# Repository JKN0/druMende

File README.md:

# druMende

Drumende is an analog drum machine in 70's style. All circuitry is designed so that it could have been built in the late 70's/early 80's.
All sound generators are analog, using transistors and op amps. Sequencer is without microcontroller, only 7400/4000-series discrete logic.

Soundgenerators are modeled according to classic drum machines and also newer designs:
- Boss DR-55: bass drum, snare drum, hi-hat, accent-circuit
- Korg KR-55: bass drum, snare drum, rimshot, claves, noise generator
- Andromeda Space Rockers by Eric Archer: hi-hat, tom hi, tom lo
- 7400 contest entry by Matt Sarnoff: sequencer

The goal has not been to duplicate the original circuits as close as possible. There are several modifications to original circuits.
Also sequencer has experienced serious modifications.

There are 10 sound generators. Because sequencer has only 6 voice channels + accent channel, sound for four channels is selectable.
Each channel level can be controlled with level control knobs. Also each channel has one controllable parameter, tuning or decay time.

Sequencer is 7 channel, 16 steps. Two 7 x 16 step patterns can be stored.

Demonstration video: https://youtu.be/f7uYuddqCkw

A more detailed build log is here: https://retroandreverse.blogspot.com/2020/12/analog-drums-beginnings-drumshave.html

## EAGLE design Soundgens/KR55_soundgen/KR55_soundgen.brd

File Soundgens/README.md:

# Sound generators

Sound generators are divided in four circuit boards:

- DR-55 soundgen
-- 3 generators: DR-55 BD, SD, HH
- KR-55 soundgen
-- 3 generators: KR-55 BD, SD; ASR MK2 HH
- Perc soundgen
-- 4 generators: KR-55 rimshot, claves; ASR MK1 hi-tom, lo-tom
- Main mixer
-- main mixer, accent submixer, accent circuit, noise generator

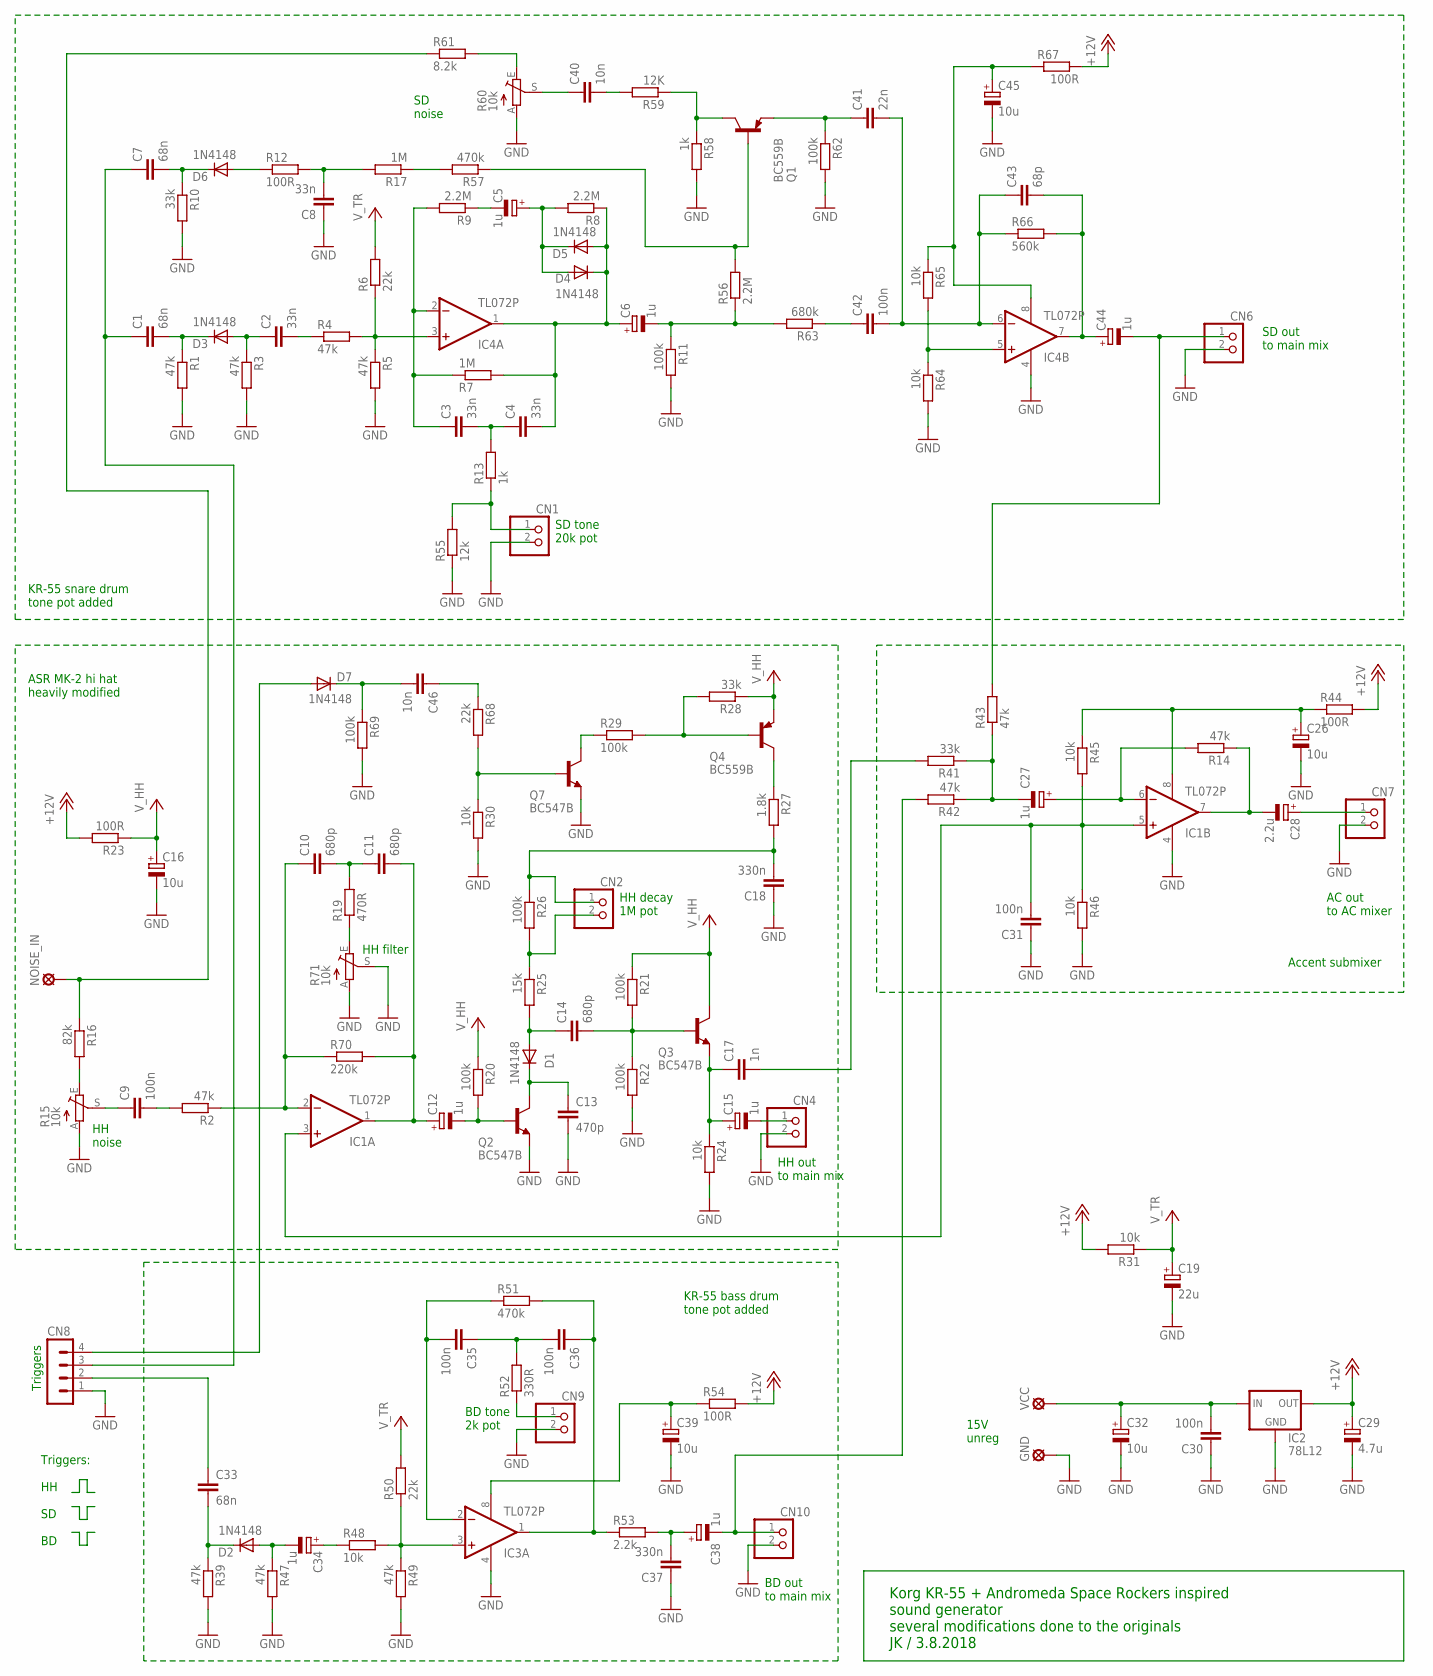
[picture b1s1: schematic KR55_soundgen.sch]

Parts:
C1, C7, C33: 68n; C0805
C2, C3, C4, C8: 33n; C0805
C5, C6, C12, C15, C27, C34, C38, C44: 1u; SMC_A
C9, C30, C31, C35, C36: 100n; C0805
C10, C11, C14: 680p; C0805
C13: 470p; C0805
C16, C32, C39, C45: 10u; E2,5-5
C17: 1n; C0805
C18, C37: 330n; C0805
C19: 22u; E2,5-5
C26: 10u; E5-5
C28: 2.2u; SMC_A
C29: 4.7u; SMC_A
C40: 10n; C1206
C41: 22n; C0805
C42: 100n; C050-024X044
C43: 68p; C0805
C46: 10n; C0805
CN1, CN2, CN4, CN6, CN7, CN9, CN10: PINHD-1X2; 1X02
CN8: MA04-1
D1, D2, D3, D4, D5, D6: 1N4148; SOD80C
D7: 1N4148; DO35-10
GND: LSP10
IC1, IC3, IC4: TL072P; DIL08
IC2: 78L12; 78LXX
NOISE_IN: LSP10
Q1, Q4: BC559B; TO92-EBC
Q2, Q3, Q7: BC547B; TO92
R1, R2, R3, R4, R5, R14, R39, R42, R43, R47, R49: 47k; R0805
R6, R50, R68: 22k; R0805
R7, R17: 1M; R0805
R8, R9, R56: 2.2M; R0805
R10, R28, R41: 33k; R0805
R11, R21, R22, R26, R29, R62, R69: 100k; R0805
R12, R23, R67: 100R; R0805
R13, R58: 1k; R0805
R15, R60, R71: 10k; S63X
R16: 82k; R0805
R19: 470R; 0207/10
R20: 100k; 0207/10
R24, R30, R31, R45, R46, R48, R64, R65: 10k; R0805
R25: 15k; 0207/10
R27: 1.8k; 0207/10
R44, R54: 100R; 0207/10
R51, R57: 470k; R0805
R52: 330R; R0805
R53: 2.2k; 0207/10
R55: 12k; R0805
R59: 12K; R0805
R61: 8.2k; R0805
R63: 680k; R0805
R66: 560k; R0805
R70: 220k; R0805
VCC: LSP10

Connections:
+12V: C29.+, IC2.OUT, R23.2, R31.2, R44.2, R54.2, R67.2
+15V: C30.2, C32.+, IC2.IN, VCC.MP
GND: C8.1, C13.2, C16.-, C18.1, C19.-, C26.-, C29.-, C30.1, C31.1, C32.-, C37.1, C39.-, C45.-, CN1.2, CN4.2, CN6.2, CN7.2, CN8.1, CN9.2, CN10.2, GND.MP, IC1.4 (V-), IC2.GND, IC3.4 (V-), IC4.4 (V-), Q2.1 (E), Q7.1 (E), R1.2, R3.2, R5.2, R10.2, R11.2, R15.A, R22.2, R24.2, R30.2, R39.2, R46.2, R47.2, R49.2, R55.1, R58.2, R60.A, R62.2, R64.2, R69.2, R71.A, R71.S
unnamed: C3.1, IC4.2 (-IN), R7.1, R9.2
unnamed: C4.2, C6.+, D4.C, D5.A, IC4.1 (OUT), R7.2, R8.1
unnamed: IC4.3 (+IN), R4.2, R5.1, R6.1
unnamed: C2.2, R4.1
unnamed: C2.1, D3.A, R3.1
unnamed: C1.2, D3.C, R1.1
unnamed: R15.E, R16.2
unnamed: CN1.1, R13.1, R55.2
unnamed: C9.1, R15.S
unnamed: C5.-, R9.1
unnamed: C5.+, D4.A, D5.C, R8.2
unnamed: R60.E, R61.2
unnamed: C9.2, R2.2
unnamed: R19.1, R71.E
unnamed: C12.-, Q2.2 (B), R20.2
unnamed: C11.2, C12.+, IC1.1 (OUT), R70.2
unnamed: C13.1, D1.C, Q2.3 (C)
unnamed: C10.1, IC1.2 (-IN), R2.1, R70.1
unnamed: C10.2, C11.1, R19.2
unnamed: C14.1, D1.A, R25.2
unnamed: C14.2, Q3.2 (B), R21.2, R22.1
unnamed: C41.2, C42.2, C43.1, IC4.6 (-IN), R66.1
unnamed: C35.2, IC3.2 (-IN), R51.1
unnamed: C15.+, C17.1, Q3.1 (E), R24.1
unnamed: CN2.2, R25.1, R26.2
unnamed: C18.2, CN2.1, R26.1, R27.2
unnamed: C8.2, R12.2, R17.2
unnamed: Q4.C, R27.1
unnamed: R17.1, R57.2
unnamed: C27.-, R41.1, R42.1, R43.1
unnamed: C28.-, IC1.7 (OUT), R14.1
unnamed: C27.+, IC1.6 (-IN), R14.2
unnamed: C36.1, IC3.1 (OUT), R51.2, R53.1
unnamed: C35.1, C36.2, R52.2
unnamed: CN9.1, R52.1
unnamed: IC3.3 (+IN), R48.2, R49.1, R50.1
unnamed: C34.+, R48.1
unnamed: C34.-, D2.A, R47.1
unnamed: C33.2, D2.C, R39.1
unnamed: C37.2, C38.+, R53.2
unnamed: C3.2, C4.1, R13.2
unnamed: C40.1, R60.S
unnamed: D6.A, R12.1
unnamed: C7.2, D6.C, R10.1
unnamed: C40.2, R59.2
unnamed: Q1.C, R58.1, R59.1
unnamed: Q1.B, R56.2, R57.1
unnamed: C6.-, R11.1, R56.1, R63.2
unnamed: C42.1, R63.1
unnamed: C41.1, Q1.E, R62.1
unnamed: IC4.5 (+IN), R64.1, R65.2
unnamed: C43.2, C44.+, IC4.7 (OUT), R66.2
unnamed: C45.+, IC4.8 (V+), R65.1, R67.1
unnamed: Q4.B, R28.2, R29.2
unnamed: Q7.3 (C), R29.1
unnamed: Q7.2 (B), R30.1, R68.2
unnamed: C46.1, R68.1
unnamed: C46.2, D7.C, R69.1
NOISE_IN: NOISE_IN.MP, R16.1, R61.1
OUT_AC: C28.+, CN7.1
OUT_BD: C38.-, CN10.1, R42.2
OUT_HH: C15.-, CN4.1
OUT_HH_AC: C17.2, R41.2
OUT_SD: C44.-, CN6.1, R43.2
TRIG_BD: C33.1, CN8.2
TRIG_HH: CN8.4, D7.A
TRIG_SD: C1.1, C7.1, CN8.3
V_BD: C39.+, IC3.8 (V+), R54.1
V_HH: C16.+, Q3.3 (C), Q4.E, R20.1, R21.1, R23.1, R28.1
V_MX: C26.+, IC1.8 (V+), R44.1, R45.1
V_MX/2: C31.2, IC1.3 (+IN), IC1.5 (+IN), R45.2, R46.1
V_TR: C19.+, R6.2, R31.1, R50.2

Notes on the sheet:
Triggers
SD tone 20k pot
HH decay 1M pot
HH out to main mix
AC out to AC mixer
15V unreg
KR-55 bass drum tone pot added
KR-55 snare drum tone pot added
ASR MK-2 hi hat heavily modified
Accent submixer
Korg KR-55 + Andromeda Space Rockers inspired sound generator several modifications done to the originals JK / 3.8.2018
SD noise
BD out to main mix
BD tone 2k pot
SD out to main mix
HH noise
HH filter
Triggers: HH SD BD

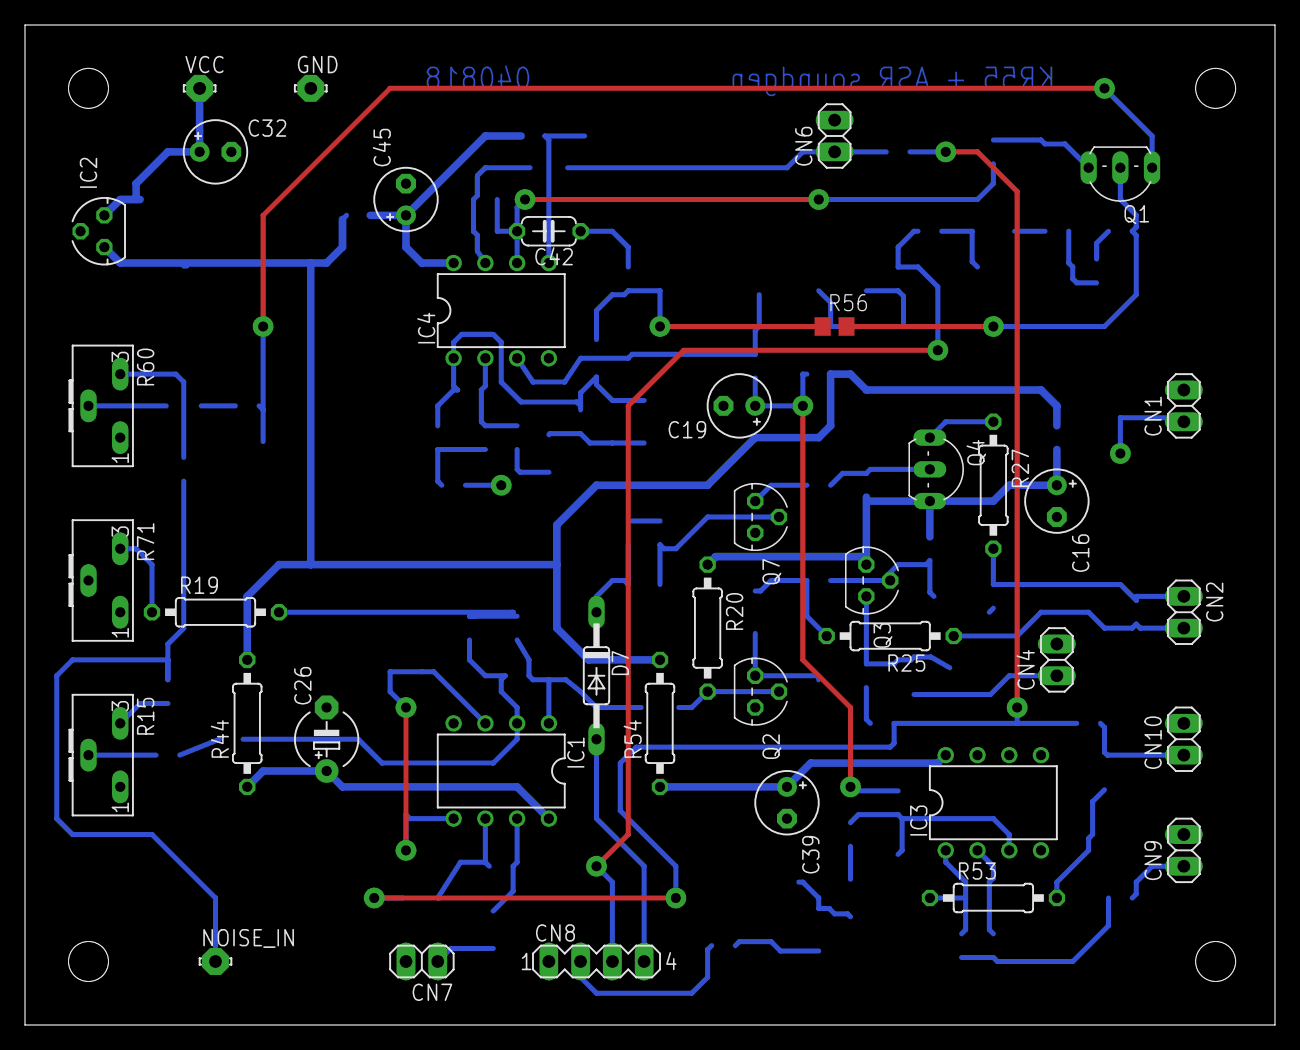
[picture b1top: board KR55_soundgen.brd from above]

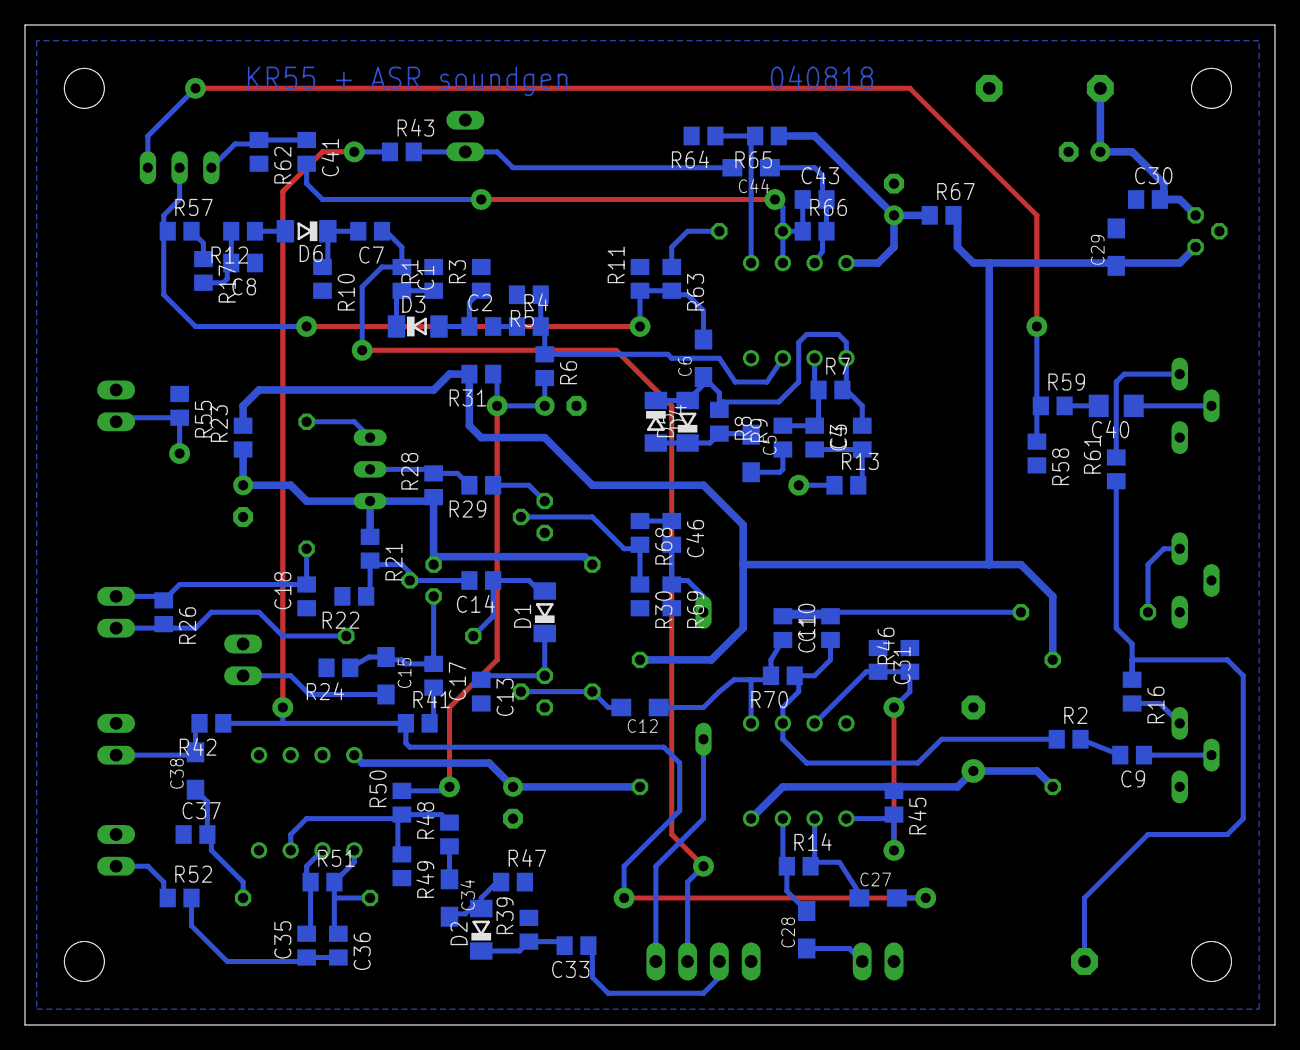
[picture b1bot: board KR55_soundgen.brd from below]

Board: 2 copper layers, 100.0 x 80.0 mm, 129 parts (90 on the bottom side), 75 nets.

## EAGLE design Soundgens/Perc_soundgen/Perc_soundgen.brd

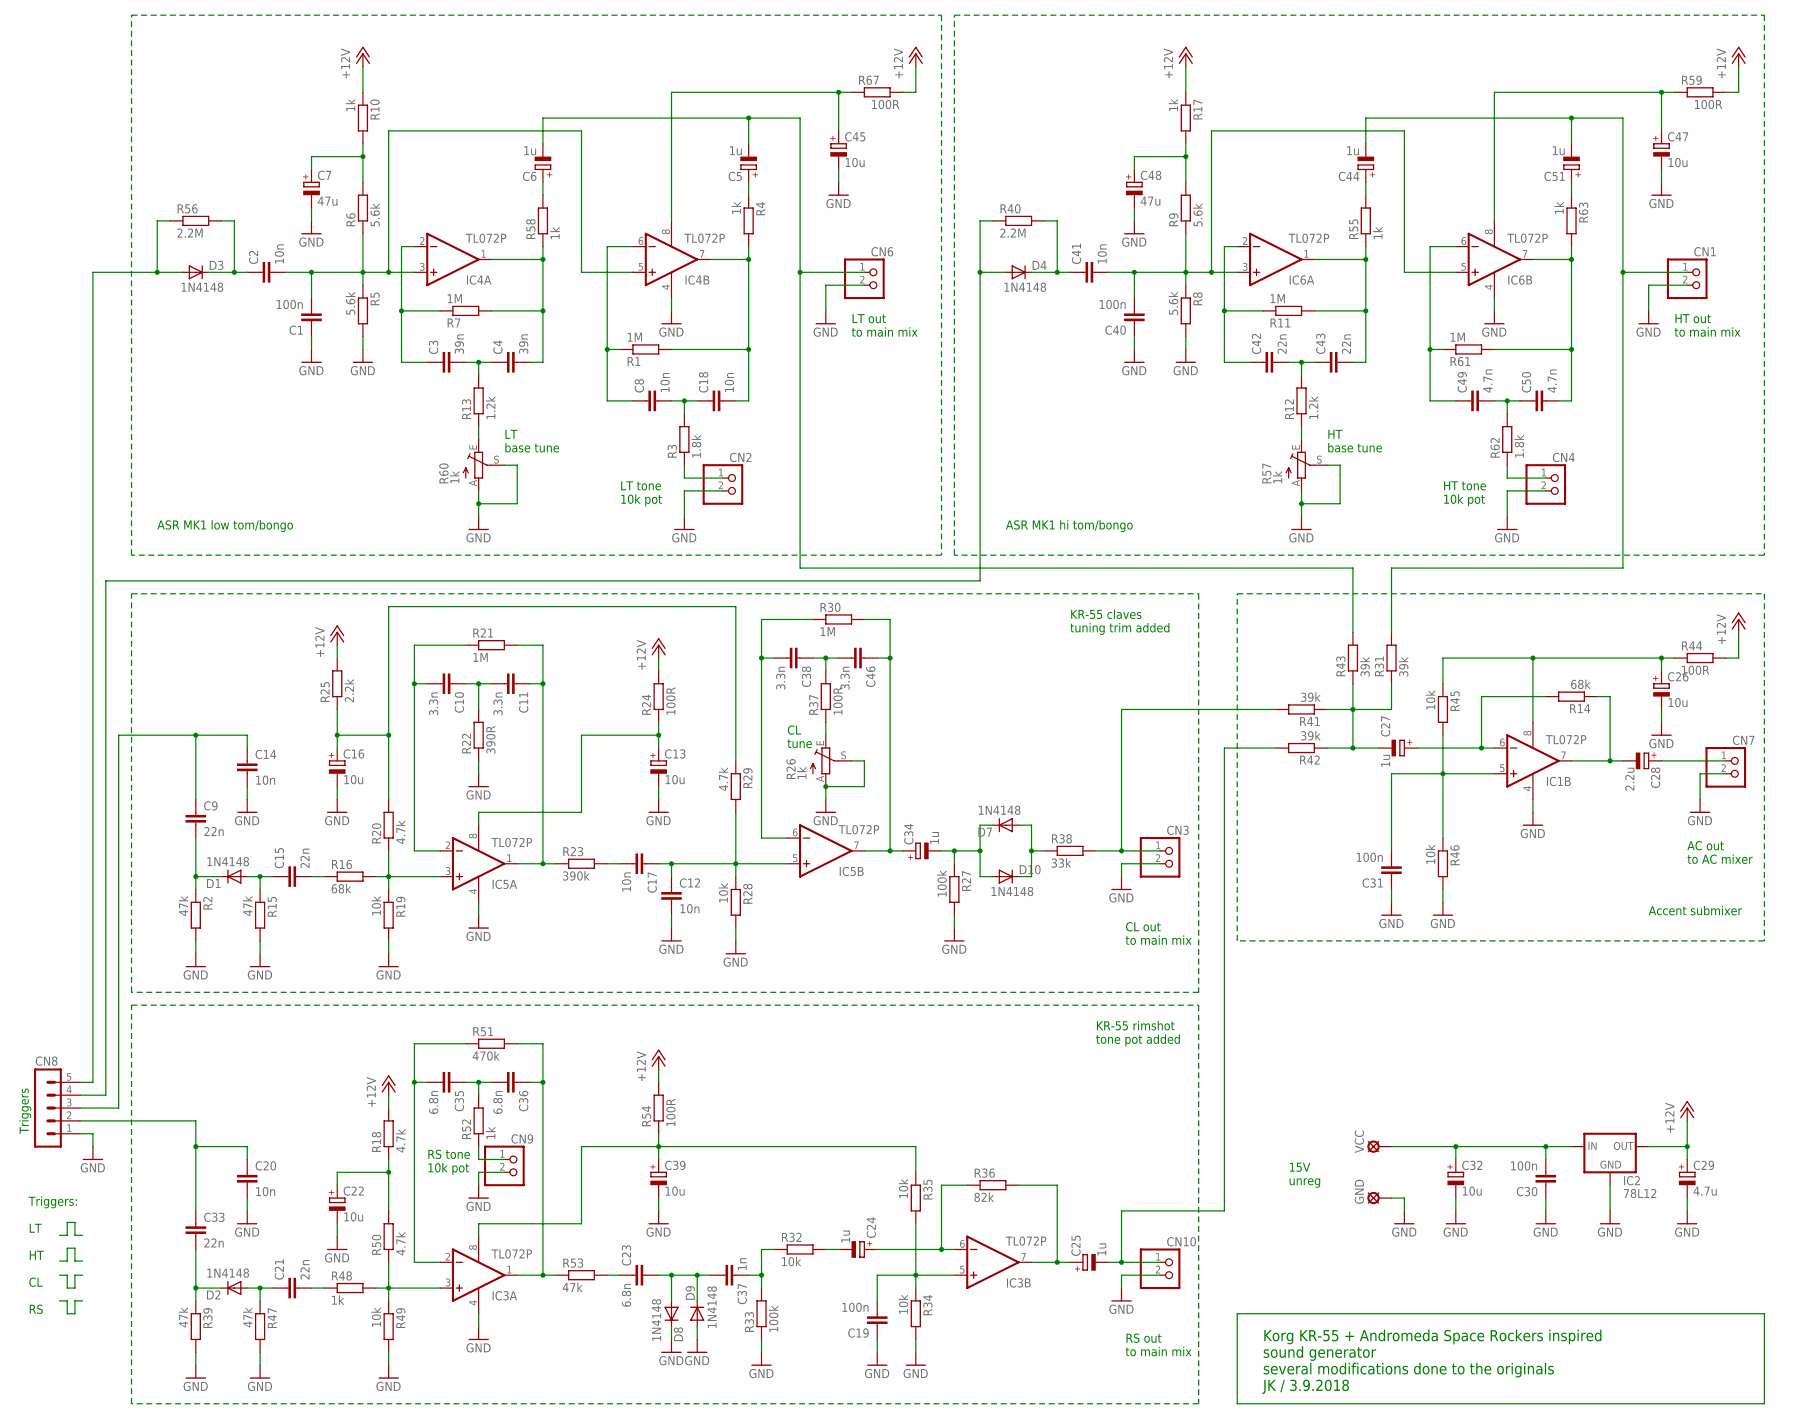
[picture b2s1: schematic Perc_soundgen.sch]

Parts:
C1, C19, C30, C31, C40: 100n; C0805
C2, C8, C12, C14, C17, C18, C20, C41: 10n; C0603
C3, C4: 39n; C0805
C5, C6, C24, C25, C27, C34, C44, C51: 1u; SMC_A
C7, C48: 47u; E2,5-5
C9, C15, C21, C42, C43: 22n; C0805
C10, C11, C38, C46: 3.3n; C0805
C13, C16, C22, C26, C32, C39, C45, C47: 10u; E2,5-5
C23, C35, C36: 6.8n; C0805
C28: 2.2u; SMC_A
C29: 4.7u; SMC_A
C33: 22n; C075-032X103
C37: 1n; C0805
C49, C50: 4.7n; C0805
CN1, CN2, CN3, CN4, CN6, CN7, CN9, CN10: PINHD-1X2; 1X02
CN8: MA05-1
D1, D2, D3, D4, D7, D8, D9, D10: 1N4148; SOD80C
GND: LSP10
IC1, IC3, IC4, IC5, IC6: TL072P; DIL08
IC2: 78L12; 78LXX
R1, R7, R11, R21, R30, R61: 1M; R0805
R2, R15, R39, R47: 47k; R0805
R3, R62: 1.8k; R0805
R4, R55, R58, R63: 1k; 0207/10
R5, R6, R8, R9: 5.6k; R0805
R10, R17, R48, R52: 1k; R0805
R12: 1.2k; R0805
R13: 1.2k; 0207/12
R14, R16: 68k; R0805
R18, R29: 4.7k; 0207/10
R19, R28, R32, R34, R35, R45, R46, R49: 10k; R0805
R20, R50: 4.7k; R0805
R22: 390R; R1206
R23: 390k; 0207/10
R24, R37, R44, R54, R59, R67: 100R; R0805
R25: 2.2k; R0805
R26, R57, R60: 1k; S63X
R27, R33: 100k; R0805
R31, R41, R42, R43: 39k; R0805
R36: 82k; R0805
R38: 33k; R0805
R40, R56: 2.2M; R0805
R51: 470k; R0805
R53: 47k; 0207/10
VCC: LSP10

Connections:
+12V: C29.+, IC2.OUT, R10.1, R17.1, R18.2, R24.2, R25.2, R44.2, R54.2, R59.2, R67.2
+15V: C30.2, C32.+, IC2.IN, VCC.MP
GND: C1.1, C7.-, C12.2, C13.-, C14.2, C16.-, C19.1, C20.2, C22.-, C26.-, C29.-, C30.1, C31.1, C32.-, C39.-, C40.1, C45.-, C47.-, C48.-, CN1.2, CN2.2, CN3.2, CN4.2, CN6.2, CN7.2, CN8.1, CN9.2, CN10.2, D8.C, D9.A, GND.MP, IC1.4 (V-), IC2.GND, IC3.4 (V-), IC4.4 (V-), IC5.4 (V-), IC6.4 (V-), R2.2, R5.2, R8.2, R15.2, R19.2, R22.1, R26.A, R26.S, R27.2, R28.2, R33.1, R34.2, R39.2, R46.2, R47.2, R49.2, R57.A, R57.S, R60.A, R60.S
unnamed: C3.1, IC4.2 (-IN), R7.1
unnamed: C4.2, IC4.1 (OUT), R7.2, R58.1
unnamed: C1.2, C2.2, IC4.3 (+IN), IC4.5 (+IN), R5.1, R6.1
unnamed: C6.+, R58.2
unnamed: C7.+, R6.2, R10.2
unnamed: C18.2, IC4.7 (OUT), R1.2, R4.2
unnamed: R13.1, R60.E
unnamed: C10.2, IC5.2 (-IN), R21.1
unnamed: C2.1, D3.C, R56.2
unnamed: C23.2, R53.2
unnamed: CN2.1, R3.1
unnamed: C11.1, IC5.1 (OUT), R21.2, R23.1
unnamed: C10.1, C11.2, R22.2
unnamed: R26.E, R37.1
unnamed: IC5.3 (+IN), R16.2, R19.1, R20.1
unnamed: C15.2, R16.1
unnamed: C15.1, D1.A, R15.1
unnamed: C9.2, D1.C, R2.1
unnamed: C16.+, R20.2, R25.1, R29.1
unnamed: C38.2, IC5.6 (-IN), R30.1
unnamed: C8.1, IC4.6 (-IN), R1.1
unnamed: C35.2, IC3.2 (-IN), R51.1
unnamed: C12.1, C17.1, IC5.5 (+IN), R28.1, R29.2
unnamed: C34.-, D7.C, D10.A, R27.1
unnamed: C34.+, C46.1, IC5.7 (OUT), R30.2
unnamed: C8.2, C18.1, R3.2
unnamed: C17.2, R23.2
unnamed: C24.+, IC3.6 (-IN), R36.1
unnamed: C22.+, R18.1, R50.2
unnamed: C24.-, R32.2
unnamed: C19.2, IC3.5 (+IN), R34.1, R35.2
unnamed: D7.A, D10.C, R38.1
unnamed: C37.1, R32.1, R33.2
unnamed: C27.-, R31.1, R41.1, R42.1, R43.1
unnamed: C28.-, IC1.7 (OUT), R14.1
unnamed: C27.+, IC1.6 (-IN), R14.2
unnamed: C23.1, C37.2, D8.A, D9.C
unnamed: C36.1, IC3.1 (OUT), R51.2, R53.1
unnamed: C35.1, C36.2, R52.2
unnamed: CN9.1, R52.1
unnamed: IC3.3 (+IN), R48.2, R49.1, R50.1
unnamed: C21.2, R48.1
unnamed: C21.1, D2.A, R47.1
unnamed: C33.2, D2.C, R39.1
unnamed: C38.1, C46.2, R37.2
unnamed: C25.+, IC3.7 (OUT), R36.2
unnamed: C3.2, C4.1, R13.2
unnamed: C5.+, R4.1
unnamed: C43.2, IC6.1 (OUT), R11.2, R55.1
unnamed: C40.2, C41.2, IC6.3 (+IN), IC6.5 (+IN), R8.1, R9.1
unnamed: C42.1, IC6.2 (-IN), R11.1
unnamed: C42.2, C43.1, R12.2
unnamed: C47.+, IC6.8 (V+), R59.1
unnamed: C48.+, R9.2, R17.2
unnamed: C41.1, D4.C, R40.2
unnamed: C50.2, IC6.7 (OUT), R61.2, R63.2
unnamed: CN4.1, R62.1
unnamed: C49.1, IC6.6 (-IN), R61.1
unnamed: C49.2, C50.1, R62.2
unnamed: R12.1, R57.E
unnamed: C45.+, IC4.8 (V+), R67.1
unnamed: C44.+, R55.2
unnamed: C51.+, R63.1
OUT_AC: C28.+, CN7.1
OUT_CL: CN3.1, R38.2, R41.2
OUT_HT: C44.-, C51.-, CN1.1, R31.2
OUT_LT: C5.-, C6.-, CN6.1, R43.2
OUT_RS: C25.-, CN10.1, R42.2
TRIG_CL: C9.1, C14.1, CN8.3
TRIG_HT: CN8.4, D4.A, R40.1
TRIG_LT: CN8.5, D3.A, R56.1
TRIG_RS: C20.1, C33.1, CN8.2
V_BD: C39.+, IC3.8 (V+), R35.1, R54.1
V_BD1: C13.+, IC5.8 (V+), R24.1
V_MX: C26.+, IC1.8 (V+), R44.1, R45.1
V_MX/2: C31.2, IC1.5 (+IN), R45.2, R46.1

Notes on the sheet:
Triggers
AC out to AC mixer
15V unreg
KR-55 rimshot tone pot added
ASR MK1 low tom/bongo
Accent submixer
Korg KR-55 + Andromeda Space Rockers inspired sound generator several modifications done to the originals JK / 3.9.2018
LT base tune
RS out to main mix
RS tone 10k pot
LT out to main mix
Triggers: LT HT CL RS
KR-55 claves tuning trim added
CL out to main mix
CL tune
LT tone 10k pot
ASR MK1 hi tom/bongo
HT base tune
HT out to main mix
HT tone 10k pot

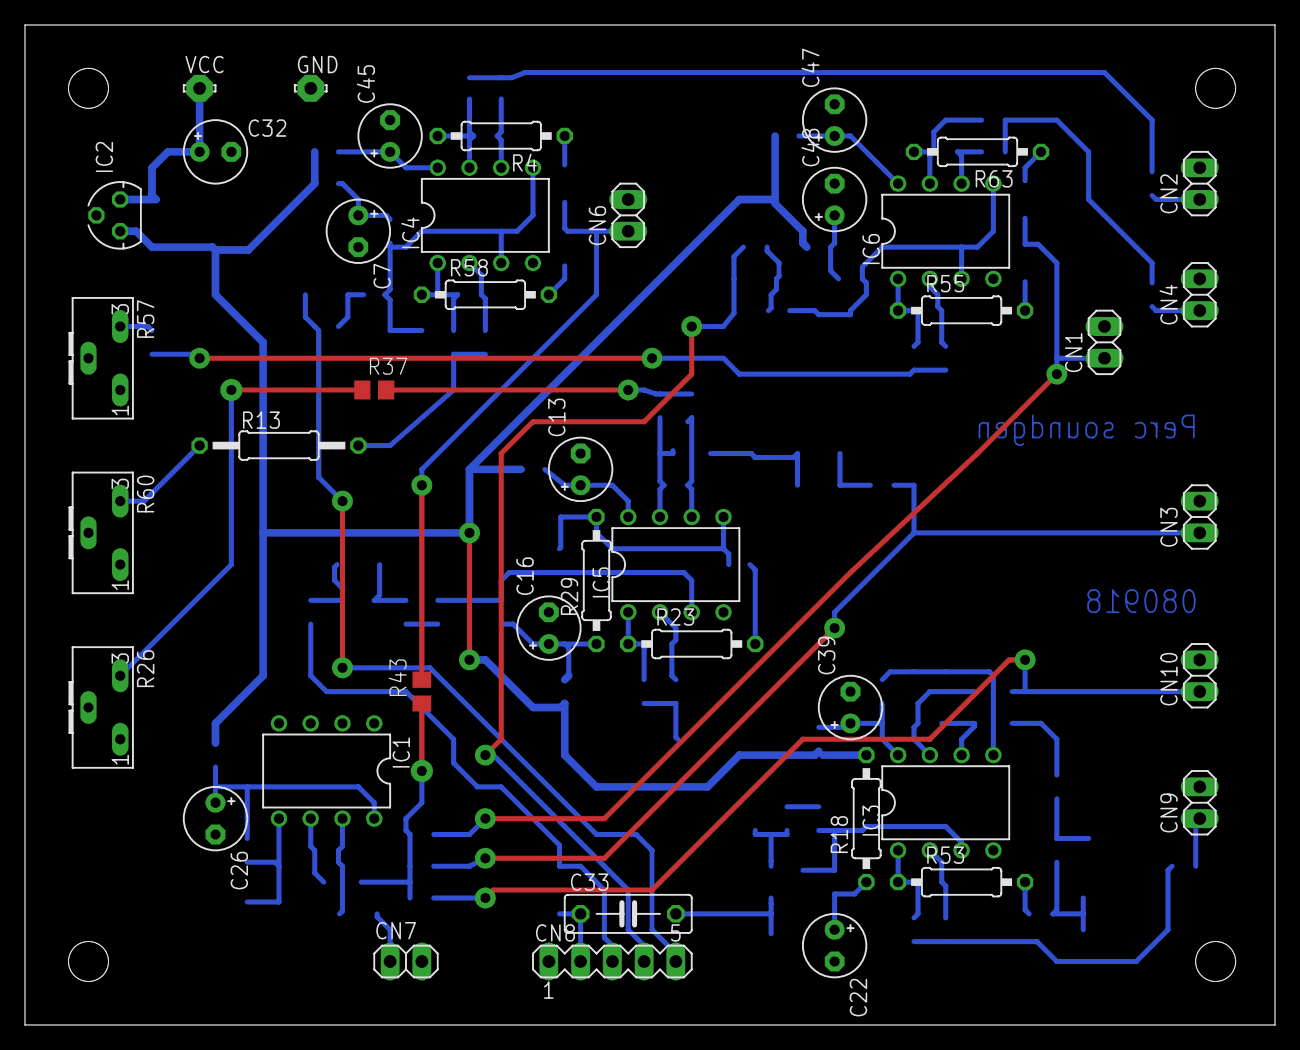
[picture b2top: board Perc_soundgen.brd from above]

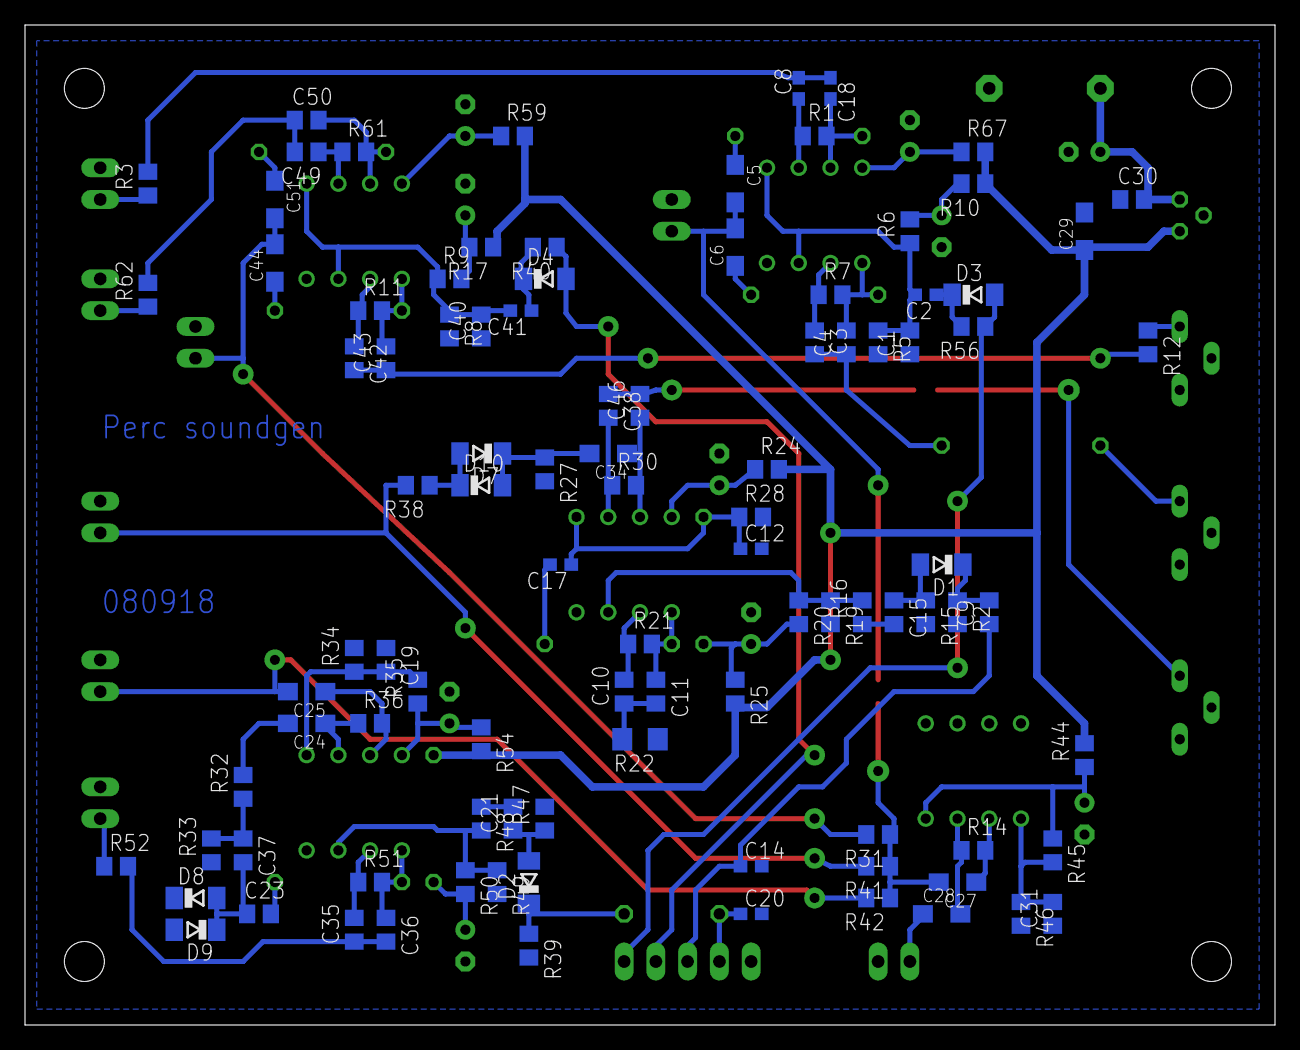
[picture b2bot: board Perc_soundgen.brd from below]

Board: 2 copper layers, 100.0 x 80.0 mm, 140 parts (98 on the bottom side), 79 nets.

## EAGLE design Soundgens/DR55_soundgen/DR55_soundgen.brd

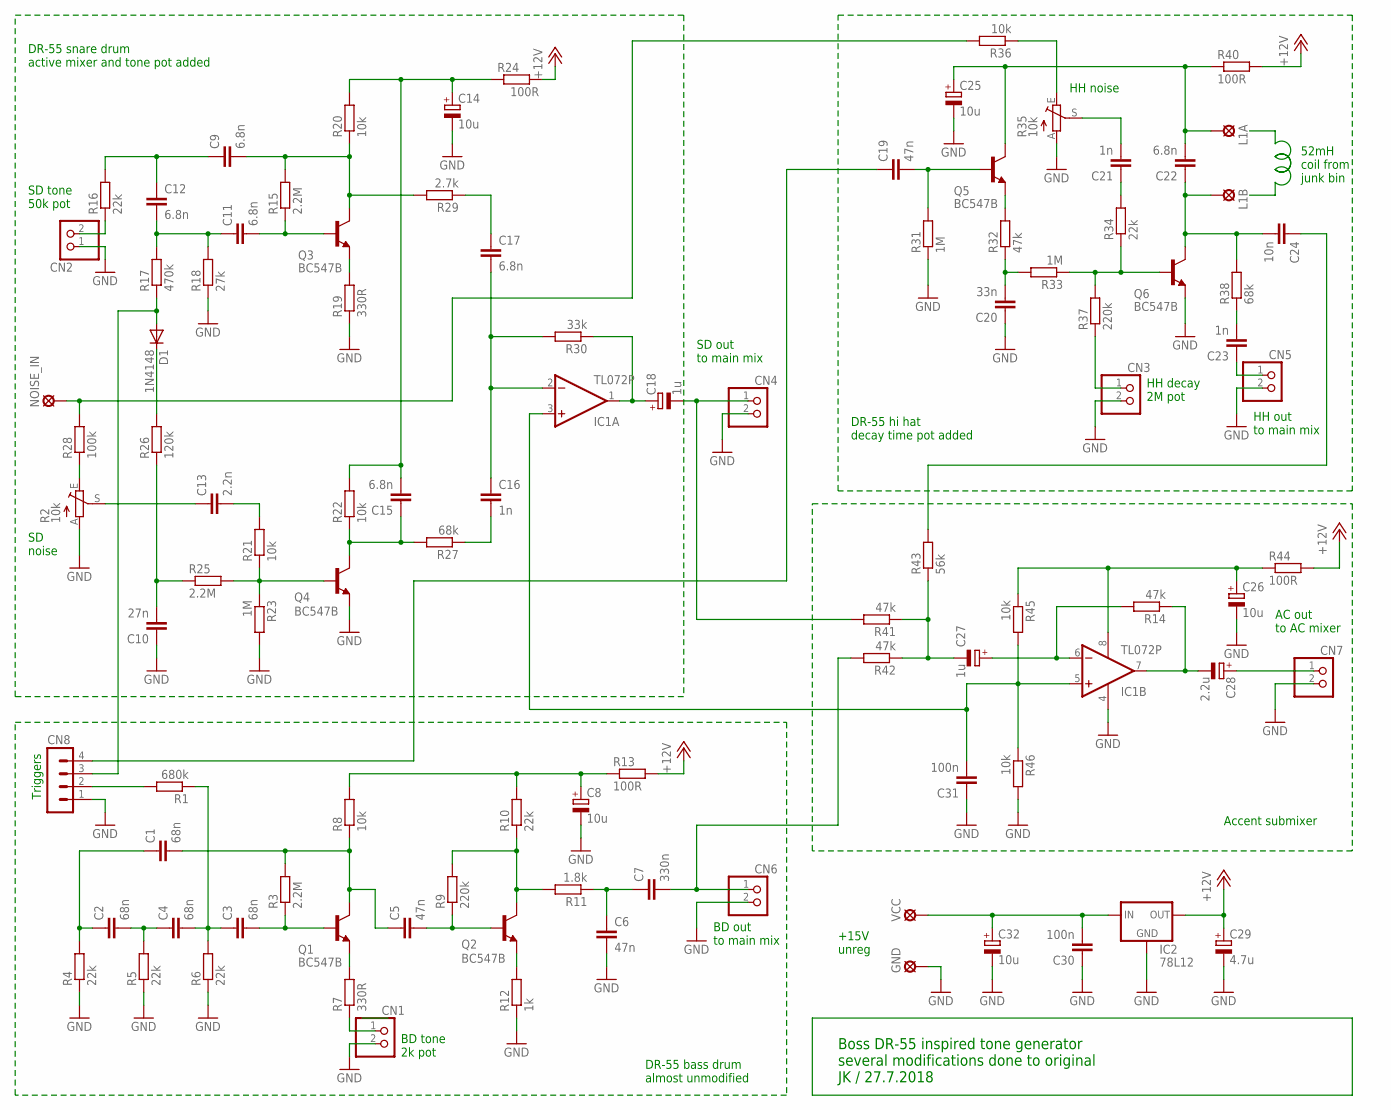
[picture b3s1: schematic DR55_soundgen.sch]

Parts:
C1, C2, C3, C4: 68n; C0805
C5, C6, C19: 47n; C0805
C7: 330n; C0805
C8, C14, C25, C26, C32: 10u; E5-5
C9, C11, C12, C17, C22: 6.8n; C0805
C10: 27n; C0805
C13: 2.2n; C0805
C15: 6.8n; C025-024X044
C16, C21, C23: 1n; C0805
C18, C27: 1u; SMC_A
C20: 33n; C0805
C24: 10n; C0805
C28: 2.2u; E5-5
C29: 4.7u; SMC_A
C30, C31: 100n; C0805
CN1, CN2, CN3, CN4, CN5, CN6, CN7: PINHD-1X2; 1X02
CN8: MA04-1
D1: 1N4148; SOD80C
GND: LSP10
IC1: TL072P; DIL08
IC2: 78L12; 78LXX
L1A, L1B: MCS10B
NOISE_IN: LSP10
Q1, Q2, Q3, Q4, Q5, Q6: BC547B; TO92
R1: 680k; R0805
R2, R35: 10k; S63X
R3, R15, R25: 2.2M; R0805
R4, R5, R6, R10, R16, R34: 22k; R0805
R7, R19: 330R; R0805
R8, R20, R21, R22, R36, R45, R46: 10k; R0805
R9, R37: 220k; R0805
R11: 1.8k; R0805
R12: 1k; R0805
R13, R24, R40, R44: 100R; R0805
R14, R41, R42: 47k; R0805
R17: 470k; R0805
R18: 27k; R0805
R23, R31, R33: 1M; R0805
R26: 120k; R0805
R27, R38: 68k; R0805
R28: 100k; R0805
R29: 2.7k; R0805
R30: 33k; R0805
R32: 47k; 0207/10
R43: 56k; R0805
VCC: LSP10

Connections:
+12V: C29.+, IC2.OUT, R13.2, R24.2, R40.2, R44.2
+15V: C30.2, C32.+, IC2.IN, VCC.MP
GND: C6.2, C8.-, C10.1, C14.-, C20.1, C25.-, C26.-, C29.-, C30.1, C31.1, C32.-, CN1.2, CN2.1, CN3.2, CN4.2, CN5.2, CN6.2, CN7.2, CN8.1, GND.MP, IC1.4 (V-), IC2.GND, Q4.1 (E), Q6.1 (E), R2.A, R4.1, R5.1, R6.1, R12.1, R18.1, R19.1, R23.2, R31.1, R35.A, R46.2
unnamed: C1.1, C2.1, R4.2
unnamed: C2.2, C4.1, R5.2
unnamed: C3.1, C4.2, R1.1, R6.2
unnamed: C3.2, Q1.2 (B), R3.1
unnamed: Q1.1 (E), R7.2
unnamed: CN1.1, R7.1
unnamed: C1.2, C5.1, Q1.3 (C), R3.2, R8.1
unnamed: C9.1, C12.1, R16.2
unnamed: C5.2, Q2.2 (B), R9.1
unnamed: R2.E, R28.1
unnamed: Q2.3 (C), R9.2, R10.1, R11.2
unnamed: Q2.1 (E), R12.2
unnamed: C6.1, C7.1, R11.1
unnamed: C11.1, C12.2, R17.2, R18.2
unnamed: C11.2, Q3.2 (B), R15.1
unnamed: Q3.1 (E), R19.2
unnamed: CN2.2, R16.1
unnamed: C9.2, Q3.3 (C), R15.2, R20.1, R29.2
unnamed: D1.C, R26.2
unnamed: C15.1, Q4.3 (C), R22.1, R27.2
unnamed: C10.2, R25.1, R26.1
unnamed: Q4.2 (B), R21.1, R23.1, R25.2
unnamed: C13.2, R21.2
unnamed: C16.2, R27.1
unnamed: C19.2, Q5.2 (B), R31.2
unnamed: C13.1, R2.S
unnamed: C17.1, R29.1
unnamed: C16.1, C17.2, IC1.2 (-IN), R30.2
unnamed: Q5.1 (E), R32.2
unnamed: C18.+, IC1.1 (OUT), R30.1
unnamed: C20.2, R32.1, R33.2
unnamed: Q6.2 (B), R33.1, R34.1, R37.2
unnamed: CN3.1, R37.1
unnamed: C22.1, C24.2, L1B.MP, Q6.3 (C), R38.2
unnamed: C23.2, R38.1
unnamed: C21.1, R34.2
unnamed: C21.2, R35.S
unnamed: R35.E, R36.1
unnamed: C27.-, R41.1, R42.1, R43.1
unnamed: C28.-, IC1.7 (OUT), R14.1
unnamed: C27.+, IC1.6 (-IN), R14.2
NOISE_IN: NOISE_IN.MP, R28.2, R36.2
OUT_AC: C28.+, CN7.1
OUT_BD: C7.2, CN6.1, R42.2
OUT_HH: C23.1, CN5.1
OUT_HH_AC: C24.1, R43.2
OUT_SD: C18.-, CN4.1, R41.2
TRIG_BD: CN8.2, R1.2
TRIG_HH: C19.1, CN8.4
TRIG_SD: CN8.3, D1.A, R17.1
V_BD: C8.+, R8.2, R10.2, R13.1
V_HH: C22.2, C25.+, L1A.MP, Q5.3 (C), R40.1
V_MX: C26.+, IC1.8 (V+), R44.1, R45.1
V_MX/2: C31.2, IC1.3 (+IN), IC1.5 (+IN), R45.2, R46.1
V_SD: C14.+, C15.2, R20.2, R22.2, R24.1

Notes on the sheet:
52mH coil from junk bin
Triggers
BD tone 2k pot
SD tone 50k pot
HH decay 2M pot
HH out to main mix
AC out to AC mixer
BD out to main mix
SD out to main mix
+15V unreg
DR-55 bass drum almost unmodified
DR-55 snare drum active mixer and tone pot added
DR-55 hi hat decay time pot added
Accent submixer
Boss DR-55 inspired tone generator several modifications done to original JK / 27.7.2018
HH noise
SD noise

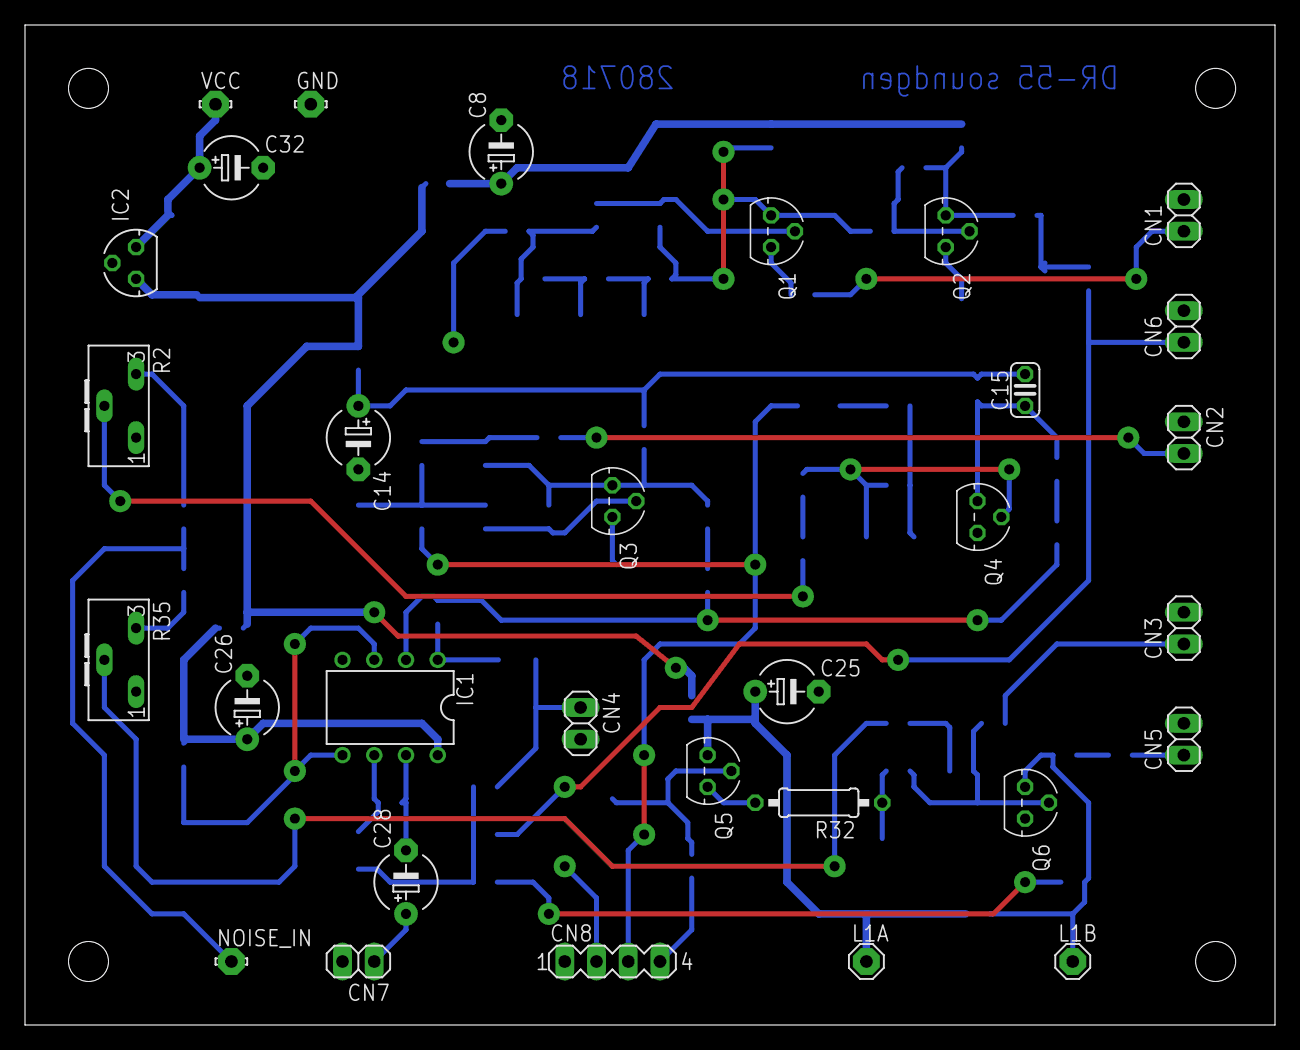
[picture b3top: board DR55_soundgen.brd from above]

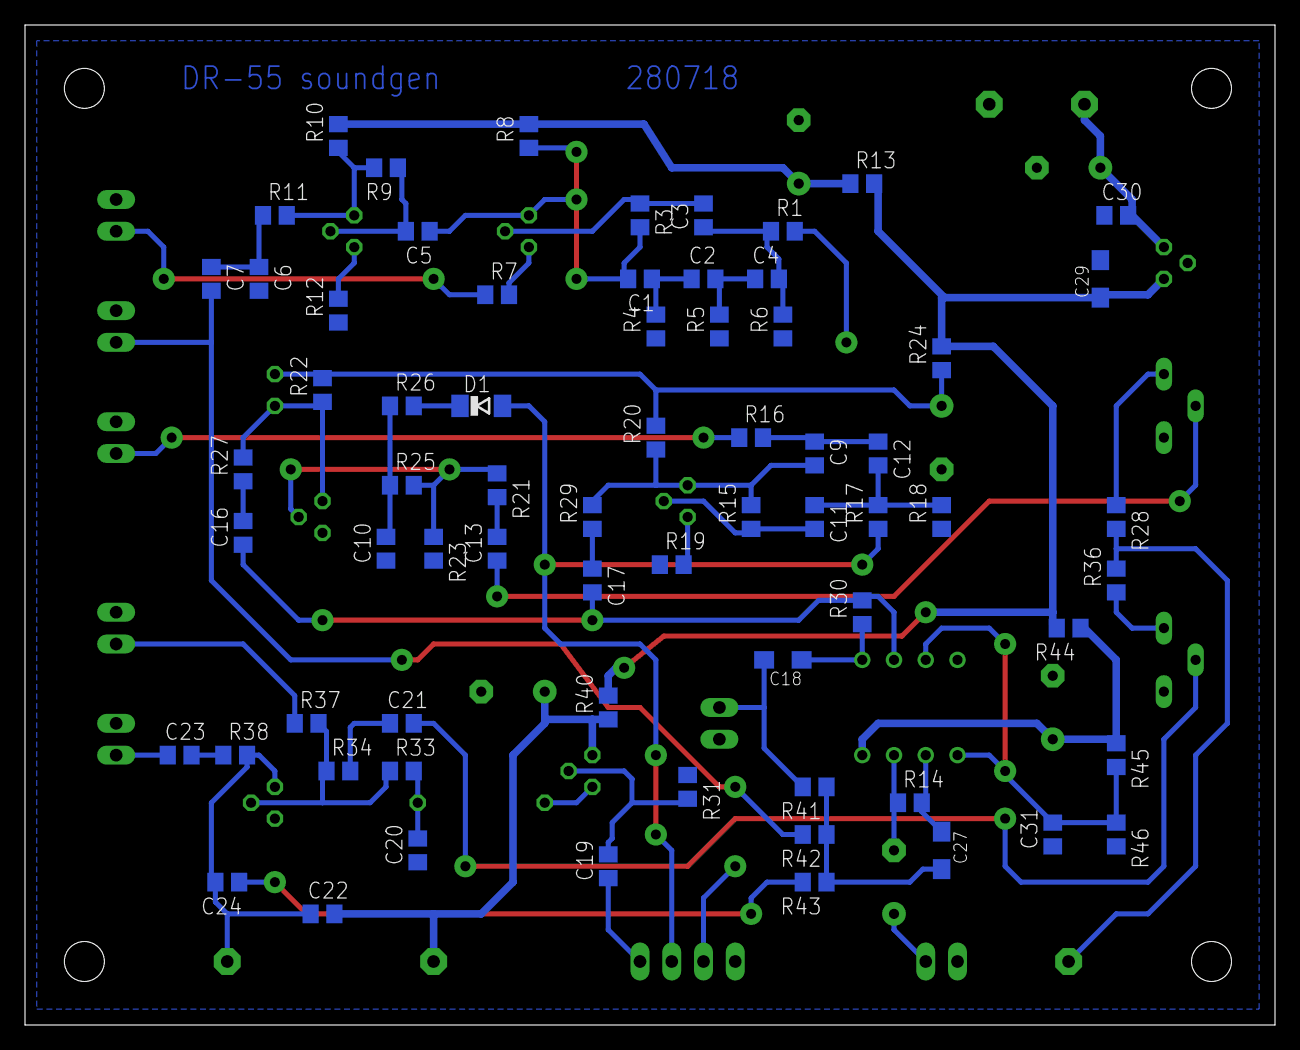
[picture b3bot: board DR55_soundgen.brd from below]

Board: 2 copper layers, 100.0 x 80.0 mm, 99 parts (68 on the bottom side), 58 nets.
